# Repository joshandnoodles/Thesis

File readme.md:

# Unnamed MS Thesis Project

An optically centric underwater wireless communication system

*This project uses the OpenROV 2.8 as a testing medium to verify the system’s ability to create a communication link in saltwater conditions. No affiliation with OpenROV has been declared. Learn more about OpenROV's vision here (http://www.openrov.com/).*

## Structure

  - **/app** *-placeholder-*
    - Chrome App source code files for debug interface
    - *not necessary for normal operation, only if debugging is needed/desired*
  - **/doc**
    - all documentation relating to the development of the system
    - **/datasheets**
      - datasheets, user-guides, schematics, and layout files for vendor components
    - **/design**
      - preliminary research of high-level design (feasibility studies, calculation notes, block diagrams, preliminary component selection tasks)
    - **/dvt**
      - design verification test of system (rework diagrams, board tracking, next generation revision notes, validation test data)
    - **/lit**
      - published papers and other external literature relevant to this project
  - **/firmware** *-placeholder-*
    - MCU firmware source code files and libraries
  - **/schema**
    - board schematic files
    - board layout files
  
## Installation

This system acts as a standalone communication system to replace the Ethernet link between two endpoints. Therefore, no software installation is needed for normal operation. Physical connections to the system will need to made to begin wireless transmission. To bring the link up, simply plug the Ethernet interface of the system into the two Ethernet ports of the endpoints to be connected (in the case of the OpenROV, the Ethernet port of the on-board BeagleBone and the Ethernet port of the PC running the Cockpit software). Then, provide power to the system using a USB on the PC side and the 3-pin adapter connector on the OpenROV side. At this point, the system will initialize and bring up the communication link independently of any user interaction.

A second installation step may be necessary if the Chrome App debug interface is needed. The source code files are located in the /app directory. Google Chrome must be installed on the PC endpoint wishing to operate the debug interface. With Chrome open, follow the steps to access the Chrome App debug interface:
  - Open Chrome and go to **Menu > (More) Tools > Extensions**
  - Click **Developer mode > Load unpacked extensions...**
  - Browse to and **Select** the **/app** directory
  - Click **Launch**

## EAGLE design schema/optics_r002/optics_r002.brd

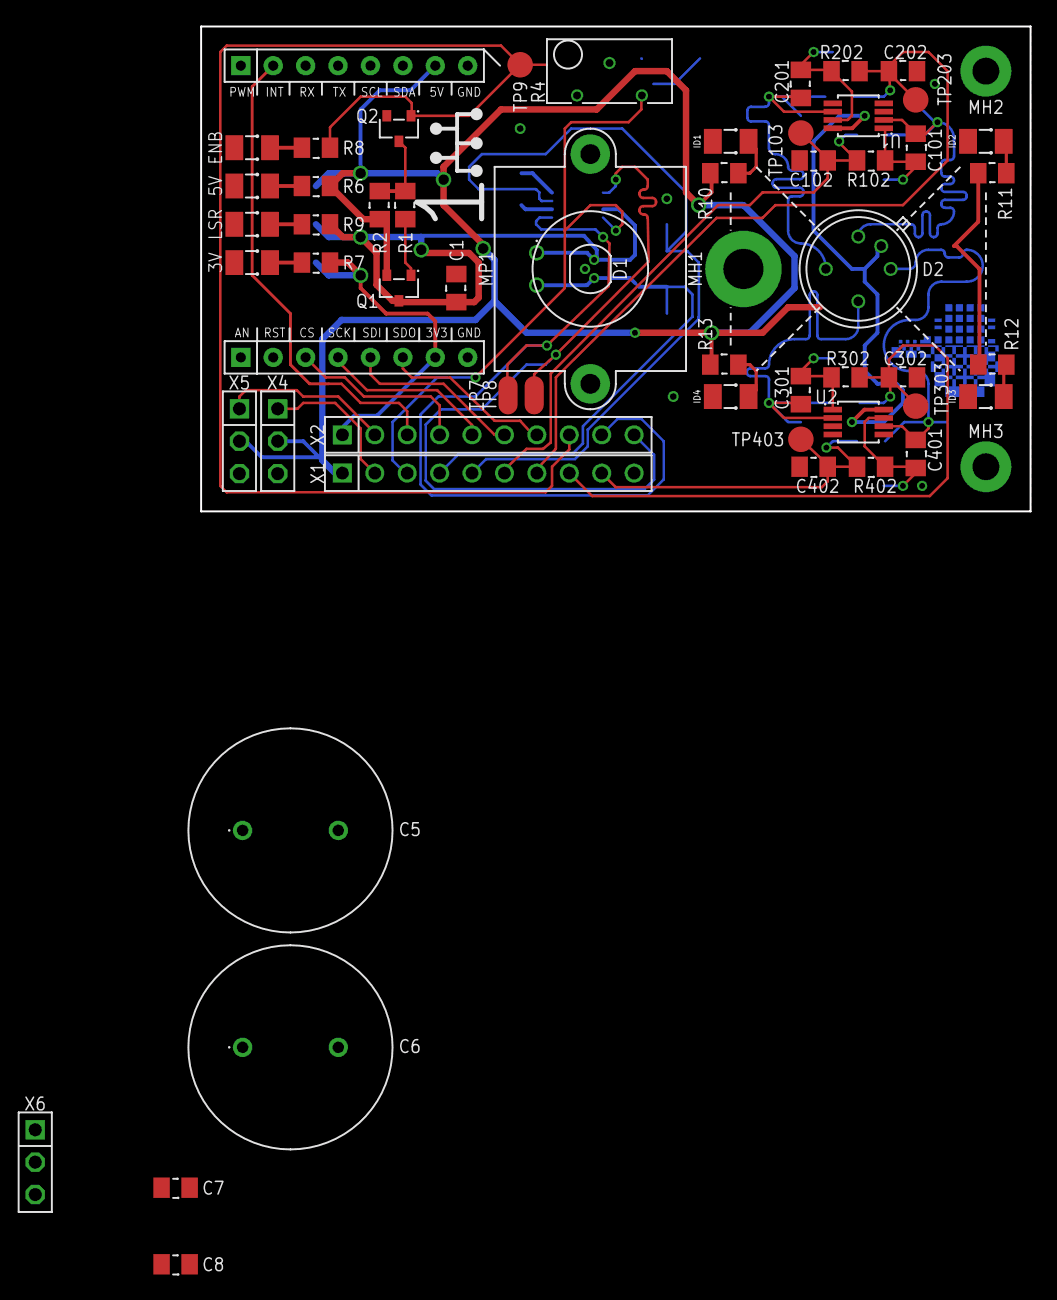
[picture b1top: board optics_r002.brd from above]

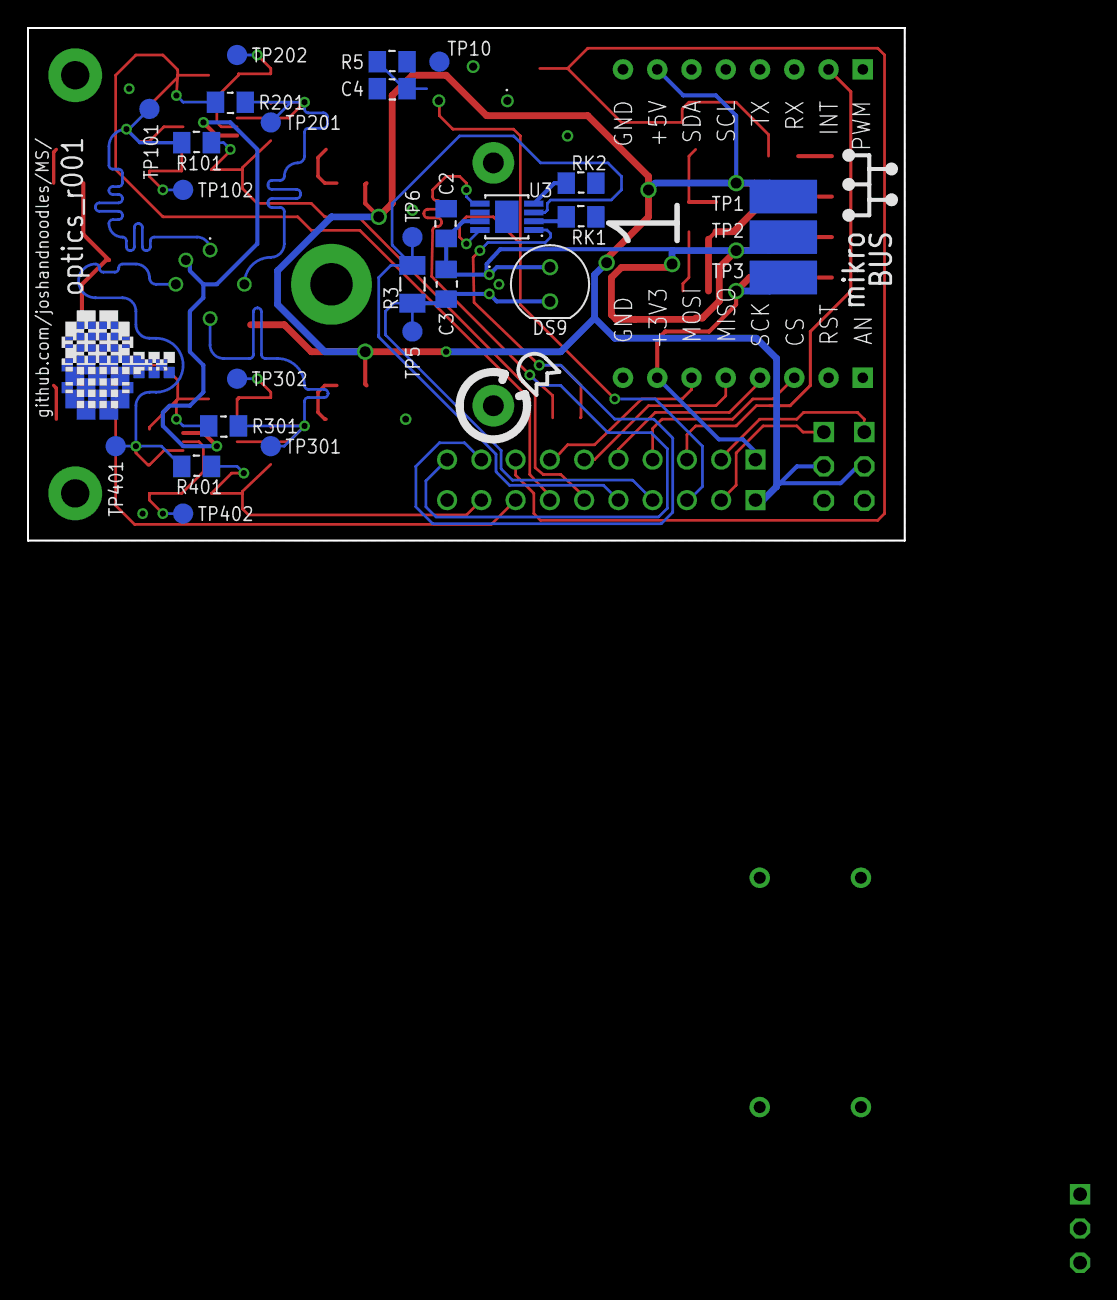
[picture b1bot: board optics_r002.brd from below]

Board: 2 copper layers, 65.0 x 38.0 mm, 86 parts (27 on the bottom side), 42 nets.

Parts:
C1: 1u; 0805_WAVE
C2, C7, C8: 0.1u; 0805_WAVE
C3: 2.2n; 0805_WAVE
C4: 47n; 0805_WAVE
C5, C6: 4700u; RADIAL_21_16_35
C101, C201, C301, C401: 2.2p; 0805_WAVE
C102, C202, C302, C402: 100p; 0805_WAVE
D1: TO38-ICUT-PL_450B
D2: TO5-QP10-6
DS1: 5V; 1206_WAVE
DS2: 3V; 1206_WAVE
DS3: ENB; 1206_WAVE
DS4: LSR; 1206_WAVE
DS5: ID1; 1206_WAVE
DS6: ID2; 1206_WAVE
DS7: ID3; 1206_WAVE
DS8: ID4; 1206_WAVE
DS9: C503B-BAN/GAN/BCN/GCN
MH1: MTG_HOLE/M3/PLATED; M3_PLATED
MH2, MH3: MTG_HOLE/M2/PLATED; M2_PLATED
MP1: V-LH09
Q1, Q2: SOT23-3
R1: 22k; 0805_WAVE
R2, R101, R201, R301, R401: 10k; 0805_WAVE
R3: 0.82; 1206_WAVE
R4: 10k; T93YB
R5: 4.7k; 0805_WAVE
R6, R11, R13: 150; 0805_WAVE
R7, R8: 68; 0805_WAVE
R9: 137; 0805_WAVE
R10, R12: 80.6; 0805_WAVE
R102, R202, R302, R402: 100; 0805_WAVE
RK1, RK2: 0; 0805_WAVE
TP1, TP2, TP3: PAD_RECT_5X2.5
TP5, TP6, TP10, TP101, TP102, TP201, TP202, TP301, TP302, TP401, TP402: PAD_CIRCLE_1.5
TP7, TP8: PAD_OVAL_3X1.5
TP9, TP103, TP203, TP303, TP403: PAD_CIRCLE_2
U1, U2: MSOP8
U3: iC-HKB; MSOP8-TP
X1, X2: 90120-0130
X3: MikroBus_3; MIKROBUS_SOCKET_NO_OUTLINE_COMPACT
X4: PAN_SERVO; 22-28-4030
X5: TILT_SERVO; 22-28-4030
X6: REWORK; 22-28-4030

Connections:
GND: C1.2, C2.2, C4.2, C5.2, C6.2, C7.2, C8.2, C102.2, C202.2, C302.2, C402.2, D1.2, DS1.2, DS2.2, DS3.2, DS4.2, DS5.2, DS6.2, DS7.2, DS8.2, MH1.1, MH2.1, MH3.1, MP1.1, MP1.2, Q2.2, R5.2, RK1.2, RK2.2, U1.3, U1.4, U1.5, U2.3, U2.4, U2.5, U3.6, U3.9, X1.10, X3.8, X3.9, X4.3, X5.3, X6.3
LED_3_3V_ANODE: DS2.1, R7.2
LED_5V_ANODE: DS1.1, R6.2
LED_5V_LSR_ANODE: DS4.1, R9.2
LED_ID1_ANODE: DS5.1, R10.2
LED_ID2_ANODE: DS6.1, R11.2
LED_ID3_ANODE: DS7.1, R12.2
LED_ID4_ANODE: DS8.1, R13.2
LED_LSR_ENB_ANODE: DS3.1, R8.2
LSR_DRV_AGND_CH1: RK1.1, U3.2
LSR_DRV_AGND_CH2: RK2.1, U3.4
LSR_ENB: Q2.1, R4.1, R8.1, TP9.1, X2.8
LSR_ENB_NMOS_DRAIN: Q2.3, R1.2, R2.2
LSR_ENB_PMOS_GATE: Q1.1, R1.1
LSR_EN_CH1: TP7.1, U3.1, X2.9
LSR_EN_CH2: TP8.1, U3.5, X2.10
LSR_ILIM_VSENSE: C4.1, R4.2, R5.1, TP10.1, U3.8, X1.3
LSR_ISENSE_LS_N: R3.2, TP6.1, U3.3, X1.5
LSR_ISENSE_LS_P: C3.2, D1.3, DS9.2, R3.1, TP5.1, X1.4
P3_3V: R7.1, TP3.1, X2.1, X3.7
P5V: C5.1, C6.1, C7.1, C8.1, Q1.2, R2.1, R6.1, R10.1, R11.1, R12.1, R13.1, TP1.1, U1.8, U2.8, X1.1, X3.10, X4.2, X5.2
P5V_LSR: C1.1, C2.1, C3.1, D1.1, DS9.1, Q1.3, R9.1, TP2.1, U3.7
P12V: D2.5, X6.1
RB1_MB2_CS: X2.4, X3.3
RD0_PWM1: X1.2, X4.1
RD3_PWM4: X2.2, X5.1
RE9_MB2_INT2: X2.3, X3.15
RG6_SPI2_SCK: X2.5, X3.4
RG7_SPI2_MISO: X2.6, X3.5
RG8_SPI2_MOSI: X2.7, X3.6
RX_AMP1_OUT: C102.1, R101.2, R102.2, TP103.1, X1.6
RX_AMP2_OUT: C202.1, R201.2, R202.2, TP203.1, X1.7
RX_AMP3_OUT: C302.1, R301.2, R302.2, TP303.1, X1.8
RX_AMP4_OUT: C402.1, R401.2, R402.2, TP403.1, X1.9
RX_OPAMP_OUT1: C101.2, R102.1, TP102.1, U1.1
RX_OPAMP_OUT2: C201.2, R202.1, TP202.1, U1.7
RX_OPAMP_OUT3: C301.2, R302.1, TP302.1, U2.1
RX_OPAMP_OUT4: C401.2, R402.1, TP402.1, U2.7
RX_QP_CH1: C101.1, D2.1, R101.1, TP101.1, U1.2
RX_QP_CH2: C201.1, D2.2, R201.1, TP201.1, U1.6
RX_QP_CH3: C301.1, D2.3, R301.1, TP301.1, U2.2
RX_QP_CH4: C401.1, D2.4, R401.1, TP401.1, U2.6

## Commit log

2016-10-10 changed image ref to github raw urls (also using https://rawgit.com/ for svg(s))
2016-10-10 removed drobox cache files
2016-10-18 added notes for weeks 6 & 7 to lab log
2016-10-18 fixed img filenames
2016-10-18 created wishlist to keep track of supply/resources needed, added J12 header to wishlist
2016-10-20 added work from weeks 8 and 9
2016-10-20 fixed svg paths for lab log
2016-10-27 added img for Week 10
2016-10-27 work from week 10
2016-10-28 inital commit readme and todo files
2016-10-28 changed version file names of img
2016-10-28 changed img locations to specific git commit (not master branch) to allow for reference of older img's in lab lab and overwritting with the same name as updates are made
2016-11-02 work from week 11
2016-11-03 work week 11
2016-11-10 work from week 12
2016-11-17 work from week 13
2016-11-18 updated em absorption literature
2016-11-20 literature review EM absorption
2016-11-20 deleted old stuff
2016-11-27 intial research on QPs from Digikey and Mouser
2016-11-28 exported comparison matrices to imgs
2016-11-28 week 14 work
2016-12-02 more em attenuation lit search
2016-12-03 more em attenuation literature review
2016-12-04 optical attenuation research/calc
2016-12-04 week 15, finals week fall 2016
2016-12-04 moving files around
2016-12-06 restructured directories & added placeholders
2016-12-08 documentation for Clicker brd & supporting products
2016-12-08 work from finals week (16) fall 2016
2016-12-22 literature searh on QPs
2016-12-22 fixed lit img paths
2017-01-05 inital spice sim commit
2017-01-10 updates for inital board design (optics_brd_r001)
2017-01-10 removed schema placeholder
2017-01-20 finialzing optics_r001 before sending to fab
2017-01-20 updated documentation before optics_r001 is sent to fab
2017-01-23 fixes to silkscreen and gerber creation
2017-01-23 swaped collimating lens (faster ship time/cheaper)
2017-01-27 creation of initial dvt/bring-up documents in anticipation of board arrival
2017-01-29 general file cleanup
2017-02-06 inital firmwire commit for laser support
2017-02-06 inital software commit for laser support, Vref monitoring, laser toggling
2017-02-07 added support for laser current sensing among other misc fixes
2017-02-07 more datasheets and dvt items and rework #1 for potentiometer fix
2017-02-07 restructured directories, new r002 sch/brd files created
2017-02-07 cleanup schematic files for creation of r002 directory
2017-02-10 updates for initial modulation testing on LD
2017-02-17 bulk adc read support w/ USB post-retrieval
2017-02-24 updated model to have realistic texturing
2017-02-28 dvt for servo current surges and fixes
2017-03-07 added waveforms testing pre- and post-amp for modulating signal
2017-03-09 debugged servo current surge issue and created workaround plan
2017-03-09 clean-up directories
2017-03-09 work from week 9
2017-03-13 qp measurements taken pre- and post-amp at distance
2017-05-10 very premliminary for half-duplex comm, data rec up on single ch
2017-05-11 not working...'
2017-05-19 half-duplex working modulation intitial commit
2017-05-23 3/4-duplex half-rate, no servo
2017-05-25 fixed img paths'
2017-05-26 investigation of overshoot ripple on lsr en channel
2017-06-06 updated reworks 1-4 to schematic r002
2017-06-08 full-duplex, 2 ch data, 4 ch alignment working state
2017-06-09 improved tracking using momentum approach
2017-06-12 testing servo PWM w/ 32-bit time base
2017-06-22 revision 1 uploaded and sent for review
